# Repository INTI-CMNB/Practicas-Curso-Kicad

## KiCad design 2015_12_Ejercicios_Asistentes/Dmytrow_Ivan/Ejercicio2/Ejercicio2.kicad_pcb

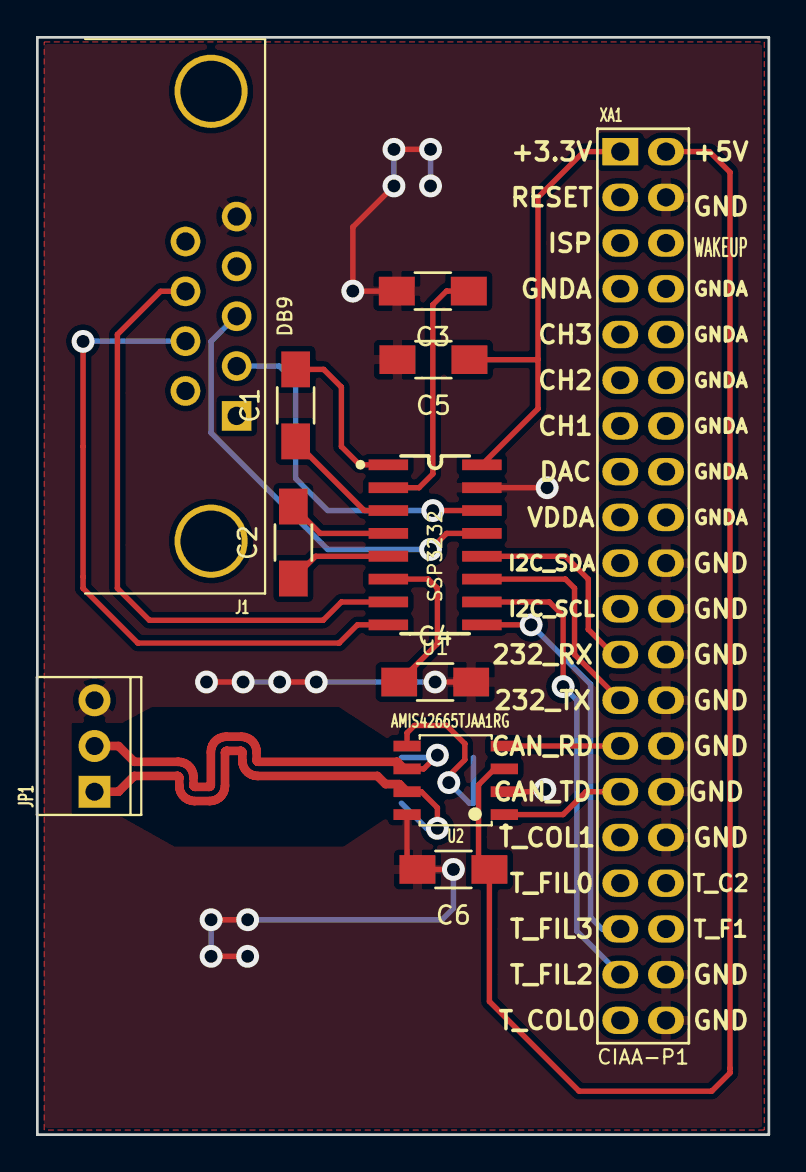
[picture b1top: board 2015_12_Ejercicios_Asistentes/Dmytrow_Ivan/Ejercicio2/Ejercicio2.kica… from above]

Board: 2 copper layers, 40.6 x 61.0 mm, 13 parts (0 on the bottom side), 22 nets.

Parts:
C1, C2, C3, C4, C5, C6: C; C_1206_HandSoldering
J1: DB9; DB9_F_TH
JP1: CONN_3; CON_PALETA_3
R1, R2: R; R_1206_HandSoldering
U1: SSP3232; SP3232ECN-SOIC16N
U2: AMIS42665TJAA1RG; SOIC-8
XA1: Conn_Poncho2P_2x_20x2; Conn_Poncho_Derecha

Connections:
+3.3V: C5.2, U1.16, XA1.1
+5V: C6.2, U2.3, XA1.2
/Conector Ycan/CAN_N: JP1.2, R2.2, U2.6
/Conector Ycan/CAN_P: JP1.1, R1.1, U2.7
/Conector Ycan/CAN_RX: U2.4, XA1.27
/Conector Ycan/CAN_TX: U2.1, XA1.29
/Conector Ycan/CTS: U1.10, XA1.37
/Conector Ycan/RTS: U1.9, XA1.35
/Conector Ycan/RXD: U1.11, XA1.25
/Conector Ycan/TXD: U1.12, XA1.23
GND: C3.1, C4.1, C5.1, C6.1, J1.5, JP1.3, U1.15, U2.2, U2.8, XA1.4, XA1.20, XA1.22, XA1.24, XA1.26, XA1.28, XA1.30, XA1.32, XA1.38, XA1.40
unnamed: C1.1, U1.1
unnamed: C1.2, U1.3
unnamed: C2.1, U1.4
unnamed: C2.2, U1.5
unnamed: C3.2, U1.2
unnamed: C4.2, U1.6
unnamed: J1.2, U1.14
unnamed: J1.3, U1.13
unnamed: J1.7, U1.8
unnamed: J1.8, U1.7
unnamed: R1.2, R2.1, U2.5

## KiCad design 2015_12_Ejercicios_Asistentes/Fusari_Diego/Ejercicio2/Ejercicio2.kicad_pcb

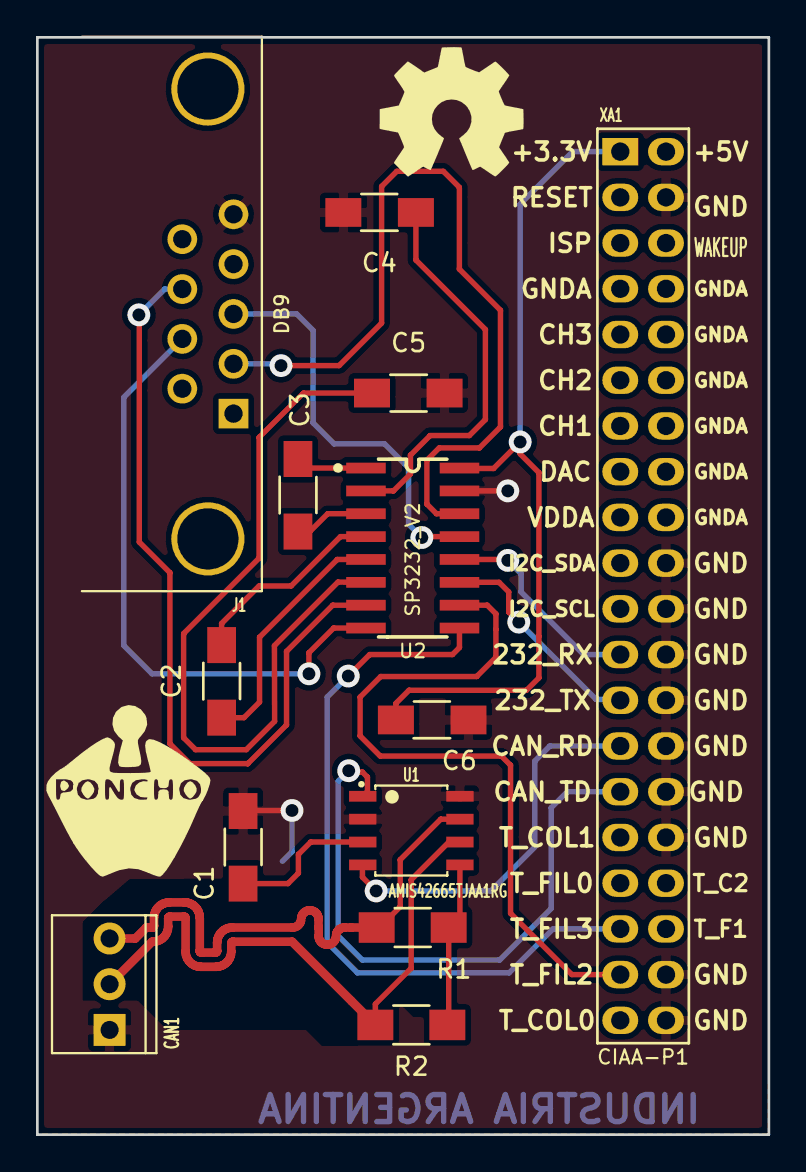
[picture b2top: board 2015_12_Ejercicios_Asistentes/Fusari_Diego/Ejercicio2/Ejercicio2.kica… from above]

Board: 4 copper layers, 40.6 x 61.0 mm, 13 parts (0 on the bottom side), 22 nets.

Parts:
C1, C2, C3, C4, C5, C6: 100nF; C_1206_HandSoldering
CAN1: J2; CON_PALETA_3
J1: DB9; DB9_F_TH
R1, R2: 60; R_1206_HandSoldering
U1: AMIS42665TJAA1RG; SOIC-8
U2: SP3232_V2; SP3232ECN-SOIC16N
XA1: Conn_Poncho2P_2x_20x2; Conn_Poncho_Derecha

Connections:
+3.3V: C6.1, U2.16, XA1.1
/Conector y CAN/CAN_N: CAN1.2, R2.2, U1.6
/Conector y CAN/CAN_P: CAN1.3, R1.1, U1.7
/Conector y CAN/CAN_RX: U1.4, XA1.27
/Conector y CAN/CAN_TX: U1.1, XA1.29
/Conector y CAN/CTS: U2.10, XA1.37
/Conector y CAN/RTS: U2.9, XA1.35
/Conector y CAN/RXD: U2.11, XA1.25
/Conector y CAN/TXD: U2.12, XA1.23
GND: C1.1, C4.1, C5.1, C6.2, CAN1.1, J1.5, U1.2, U1.8, U2.15, XA1.4, XA1.20, XA1.22, XA1.24, XA1.26, XA1.28, XA1.30, XA1.32, XA1.38, XA1.40
unnamed: C1.2, U1.3
unnamed: C2.1, U2.4
unnamed: C2.2, U2.5
unnamed: C3.1, U2.1
unnamed: C3.2, U2.3
unnamed: C4.2, U2.2
unnamed: C5.2, U2.6
unnamed: J1.2, U2.14
unnamed: J1.3, U2.13
unnamed: J1.7, U2.8
unnamed: J1.8, U2.7
unnamed: R1.2, R2.1, U1.5

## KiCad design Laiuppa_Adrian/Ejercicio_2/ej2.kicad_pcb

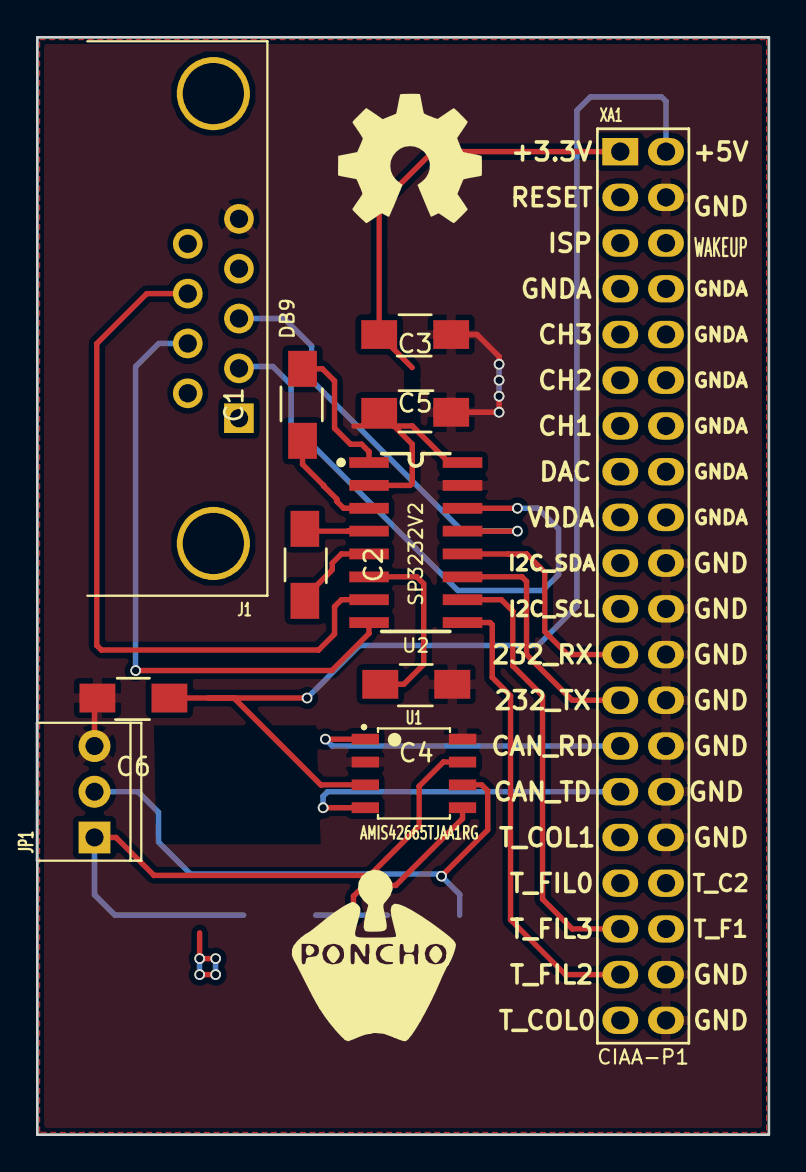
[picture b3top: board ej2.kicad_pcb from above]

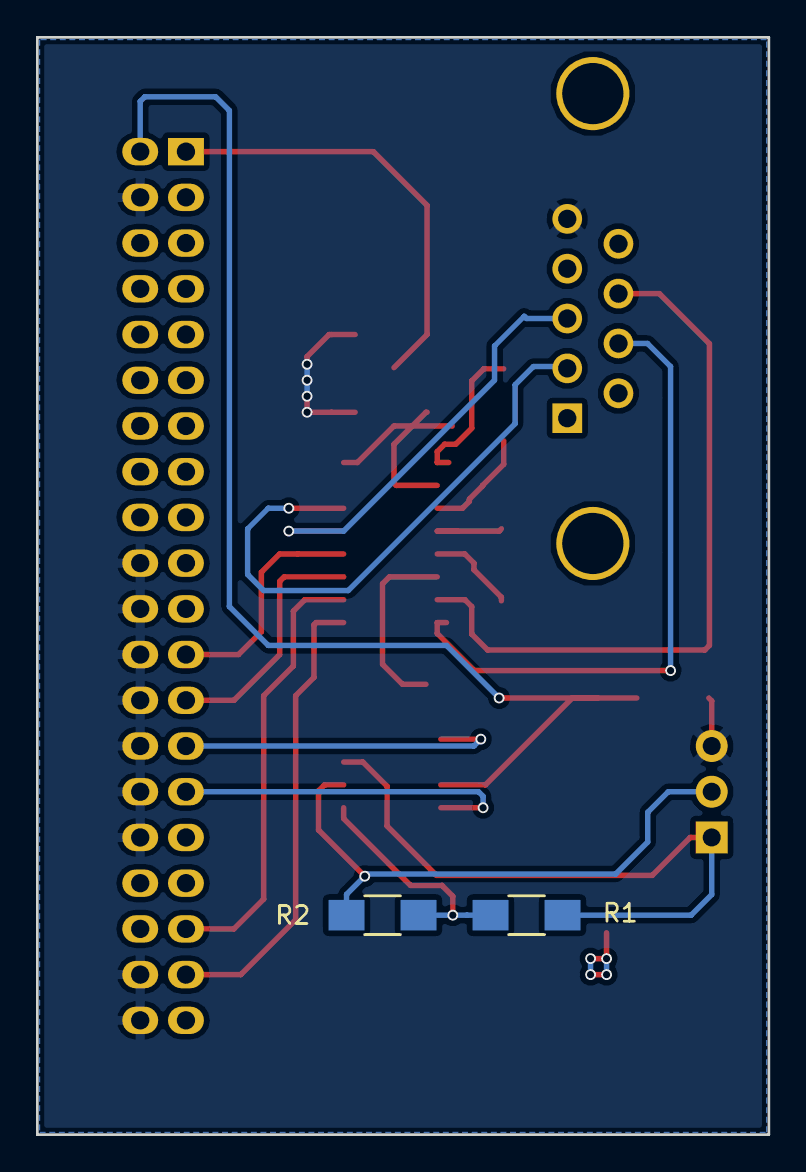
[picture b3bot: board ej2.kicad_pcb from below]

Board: 2 copper layers, 40.6 x 61.0 mm, 14 parts (2 on the bottom side), 22 nets.

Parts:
C1, C2, C3, C4, C5: C; C_1206_HandSoldering
C6: 100uF; C_1206_HandSoldering
G101: Logo_OSHWA
J1: DB9; DB9_F_TH
JP1: CONN_3; CON_PALETA_3
R1, R2: 60; R_1206_HandSoldering
U1: AMIS42665TJAA1RG; SOIC-8
U2: SP3232V2; SP3232ECN-SOIC16N
XA1: Conn_Poncho2P_2x_20x2; Conn_Poncho_Derecha

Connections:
+3.3V: C5.1, U2.16, XA1.1
+5V: C6.2, U1.3, XA1.2
/conector y can/CAN_N: JP1.2, R2.2, U1.6
/conector y can/CAN_P: JP1.1, R1.1, U1.7
/conector y can/CAN_RX: U1.4, XA1.29
/conector y can/CAN_TX: U1.1, XA1.27
/conector y can/CTS: U2.10, XA1.35
/conector y can/RTS: U2.9, XA1.37
/conector y can/RXD: U2.11, XA1.25
/conector y can/TXD: U2.12, XA1.23
GND: C3.1, C4.2, C5.2, C6.1, J1.5, JP1.3, U1.2, U1.8, U2.15, XA1.4, XA1.20, XA1.22, XA1.24, XA1.26, XA1.28, XA1.30, XA1.32, XA1.38, XA1.40
unnamed: C1.1, U2.1
unnamed: C1.2, U2.3
unnamed: C2.1, U2.5
unnamed: C2.2, U2.4
unnamed: C3.2, U2.2
unnamed: C4.1, U2.6
unnamed: J1.2, U2.14
unnamed: J1.3, U2.13
unnamed: J1.7, U2.8
unnamed: J1.8, U2.7
unnamed: R1.2, R2.1, U1.5
